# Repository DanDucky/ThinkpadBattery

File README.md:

# ThinkpadBattery
Open source Thinkpad battery design

## Fork scope
- Refactor firmware to make use of some of C++'s templating features to make it more readable and better documented.
- Redesign board to use a thermistor and connect directly to the 7 pin connector. Possibly use a battery gas gauge.
- Redesign case to more cleanly incorporate the board and a recommended BMS.
- Provide better documentation on the Thinkpad's specific smart battery protocol instructions.

## What is this?

This is a fully open source laptop battery design. The design uses an attiny85, which can reply to the T420 motherboard's SMBUS requests.

## Setup

### Configurable Constants

- BATTERY_CAPACITY | Your battery capacity in mAH
- V_HIGH | The highest output voltage of your battery, normally 12.6v
- V_LOW | The cutoff for when the battery will stop working, normally around 10.8v

### Creating your own

Parts Needed
- Arduino Uno/Mega  (for programming the attiny85, Mega needs different pin assignment)
- 12v Lithium-Ion battery pack
- 3S Lithium-Ion BMS (it might be possible to use the existing bms if specification is available but communication needs to be implemented)
- Components from schematic
- PCB from schematic

Once you have all these parts, assemble the pcb and attach a BMS to your battery pack. Solder the 12v battery output/input to the large pads on the pcb, then program the attiny85 with the included ino file. The output pins at the bottom of the PCB are a 1-1 mapping of the motherboard pin input.

### Debugging

- The laptop won't supply power to the board unless it detects there's a battery attached, meaning if you plug the board in to the battery without having an external battery to power it, it won't work.

### Libraries

Use the ATTinyCore for compiling. Without it, Wire.h won't work.

## Limitations

### Voltage Reading / Remaining battery

Currently remaining battery %'s aren't exact because I'm assuming there is a linear coorelation between voltage and capacity (Which is wrong). This is probably fixable using a battery gas gauge, I'll have to investiage more.

### MCU Power Consumption

By design, the MCU will always be on as long as a battery is connected to it. This can cause the battery to slowly run out of power if it isn't connected to a laptop. A potential fix could be to implement a low power mode for the attiny, or have a seperate disconnect switch for the battery power on the battery pack itself.

### 3D Printable Case for T420 only

The case for the cells has been completed. The case model and stl files are included in /model

## Future Plans

iam4722202468 - Design and manufacture a PCB with current,voltage and battery capacity measuring capabilities, an easily programmable microcontroller, and a 3s balanced charger

pj1976 - Find a bms that would fit, or try to talk with bq29312pw that was in the original pack

## Credits

iam4722202468 - Initial work, T420 9 cell model

pj1976 - Added support for R50

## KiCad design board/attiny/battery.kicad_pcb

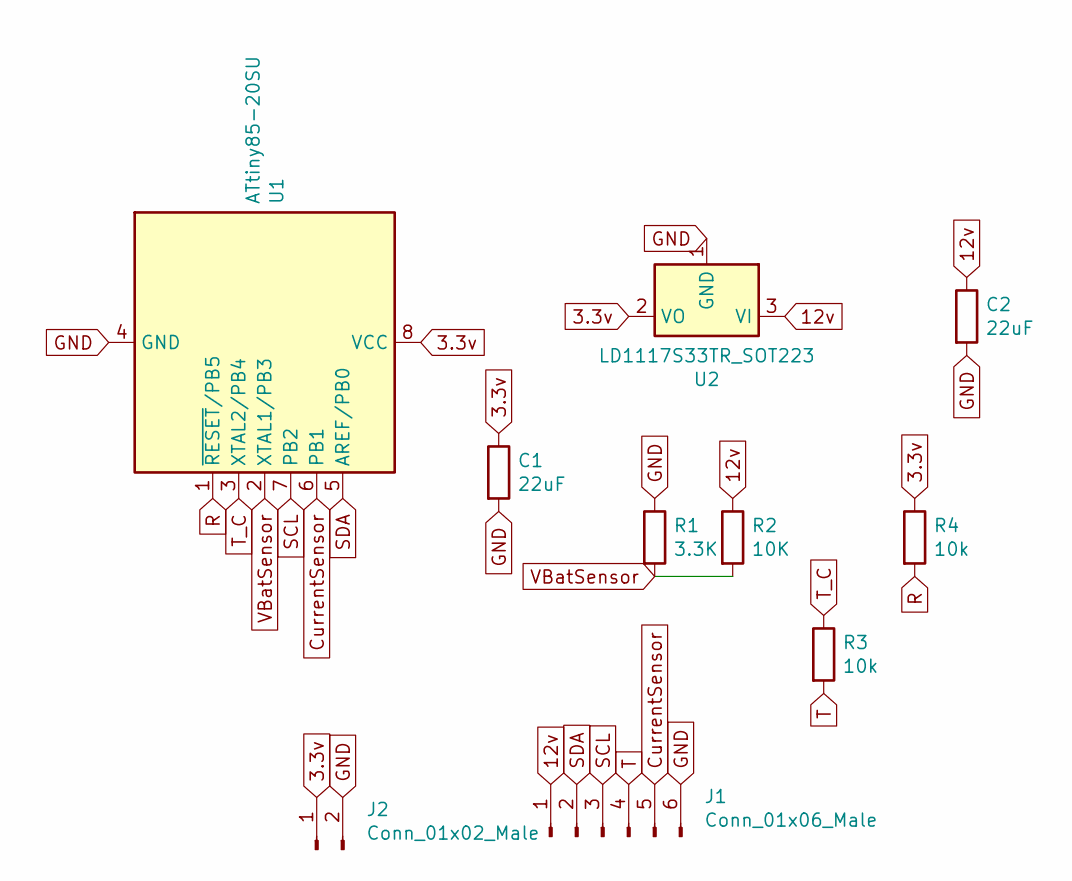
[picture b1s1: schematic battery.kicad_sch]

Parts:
C1, C2: 22uF; C_0805_2012Metric
J1: Conn_01x06_Male; PinHeader_1x06_P2.54mm_Horizontal
J2: Conn_01x02_Male; PinHeader_1x02_P2.54mm_Vertical
R1: 3.3K; R_0402_1005Metric
R2: 10K; R_0402_1005Metric
R3, R4: 10k; R_0402_1005Metric
U1: ATtiny85-20SU; SOIJ-8_5.3x5.3mm_P1.27mm
U2: LD1117S33TR_SOT223; SOT-223-3_TabPin2

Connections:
3.3v: C1.1, J2.1, R4.1, U1.8 (VCC), U2.2 (VO)
12v: C2.1, J1.1, R2.1, U2.3 (VI)
CurrentSensor: J1.5, U1.6 (PB1)
GND: C1.2, C2.2, J1.6, J2.2, R1.1, U1.4 (GND), U2.1 (GND)
R: R4.2, U1.1 (~RESET/PB5)
SCL: J1.3, U1.7 (PB2)
SDA: J1.2, U1.5 (AREF/PB0)
T: J1.4, R3.2
T_C: R3.1, U1.3 (XTAL2/PB4)
VBatSensor: R1.2, R2.2, U1.2 (XTAL1/PB3)

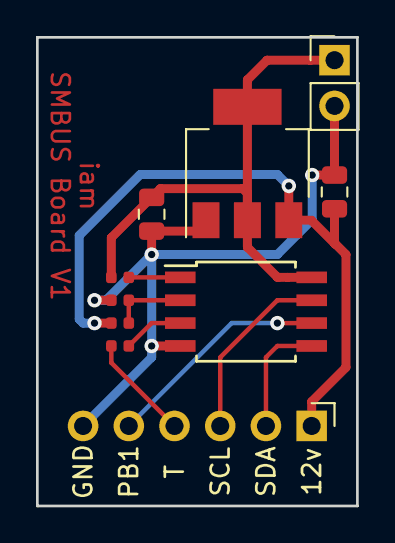
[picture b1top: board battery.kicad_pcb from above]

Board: 2 copper layers, 17.8 x 26.0 mm, 10 parts (0 on the bottom side), 10 nets.

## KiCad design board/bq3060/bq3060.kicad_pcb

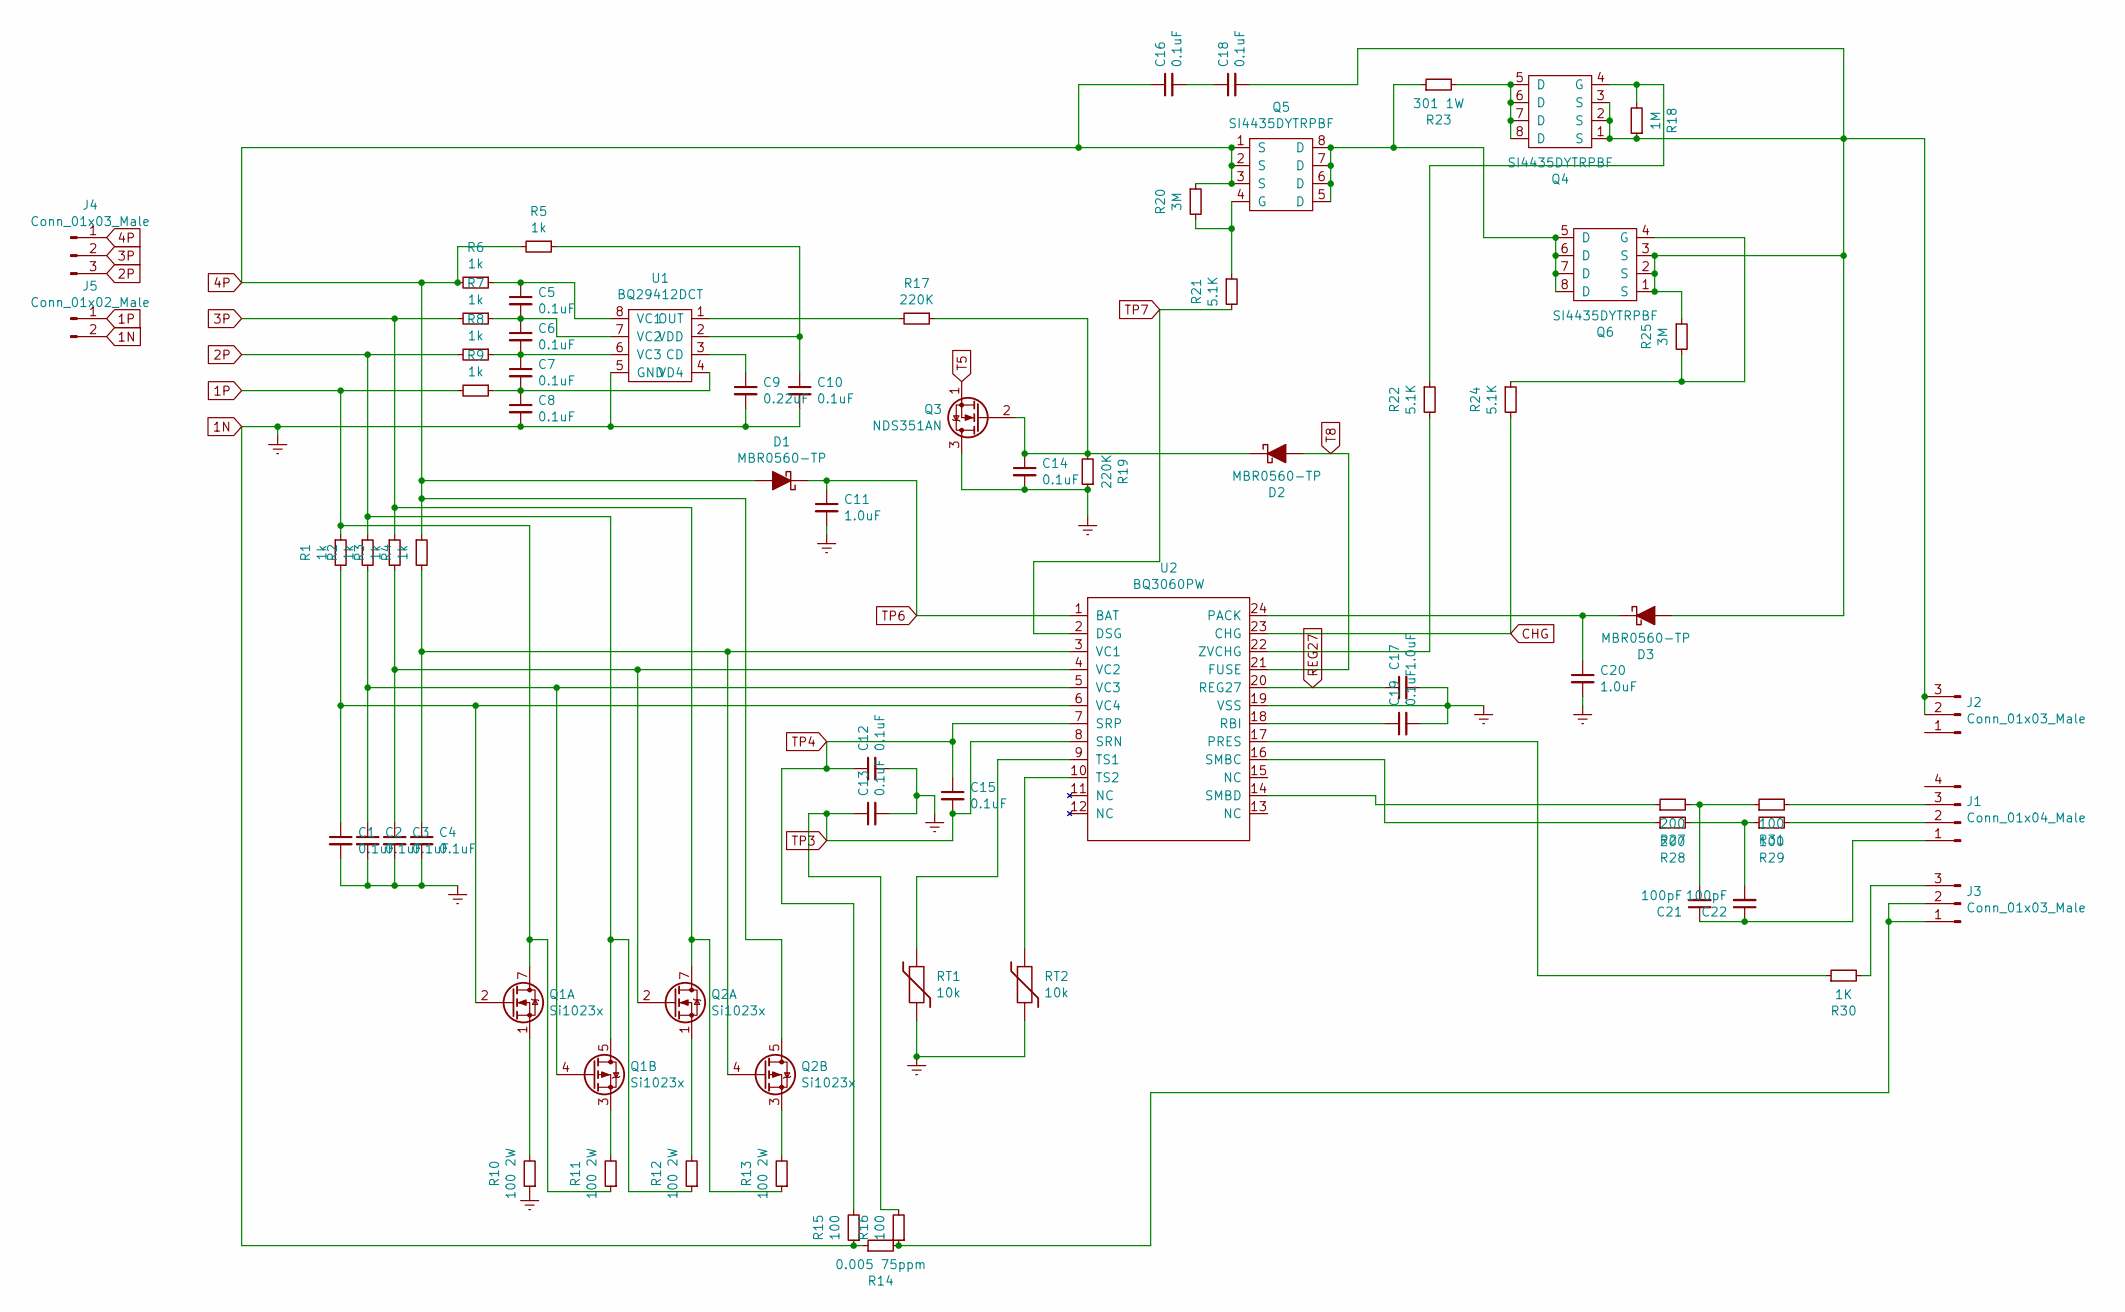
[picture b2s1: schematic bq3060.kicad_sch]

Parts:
C1, C2, C3, C4, C5, C6, C7, C8, C10, C12, C13, C14, C15, C16, C18, C19: 0.1uF; C_0805_2012Metric_Pad1.15x1.40mm_HandSolder
C9: 0.22uF; C_0805_2012Metric_Pad1.15x1.40mm_HandSolder
C11, C17, C20: 1.0uF; C_0805_2012Metric_Pad1.15x1.40mm_HandSolder
C21, C22: 100pF; C_0805_2012Metric_Pad1.15x1.40mm_HandSolder
D1, D2, D3: MBR0560-TP; D_SOD-123
J1: Conn_01x04_Male; PinHeader_1x04_P2.54mm_Horizontal
J2, J3: Conn_01x03_Male; PinHeader_1x03_P2.54mm_Vertical
J4: Conn_01x03_Male; SolderWirePad_1x03_P5.715mm_Drill2mm
J5: Conn_01x02_Male; SolderWirePad_1x02_P7.62mm_Drill2mm
Q1, Q2: Si1023x; SOIC-8_3.9x4.9mm_P1.27mm
Q3: NDS351AN; SOT-23
Q4, Q5, Q6: SI4435DYTRPBF; SOIC-8_3.9x4.9mm_P1.27mm
R1, R2, R3, R4, R5, R6, R7, R8, R9: 1k; R_0805_2012Metric_Pad1.15x1.40mm_HandSolder
R10, R11, R12, R13: 100 2W; R_2512_6332Metric_Pad1.52x3.35mm_HandSolder
R14: 0.005 75ppm; R_2512_6332Metric_Pad1.52x3.35mm_HandSolder
R15, R16, R29, R31: 100; R_0805_2012Metric_Pad1.15x1.40mm_HandSolder
R17, R19: 220K; R_0805_2012Metric_Pad1.15x1.40mm_HandSolder
R18: 1M; R_0805_2012Metric_Pad1.15x1.40mm_HandSolder
R20, R25: 3M; R_0805_2012Metric_Pad1.15x1.40mm_HandSolder
R21, R22, R24: 5.1K; R_0805_2012Metric_Pad1.15x1.40mm_HandSolder
R23: 301 1W; R_2512_6332Metric_Pad1.52x3.35mm_HandSolder
R27, R28: 200; R_0805_2012Metric_Pad1.15x1.40mm_HandSolder
R30: 1K; R_0805_2012Metric_Pad1.15x1.40mm_HandSolder
RT1, RT2: 10k; R_0805_2012Metric_Pad1.15x1.40mm_HandSolder
U1: BQ29412DCT; SN74LVC2G241_DCT_8
U2: BQ3060PW; TSSOP-24_4.4x7.8mm_P0.65mm

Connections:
1N: C1.2, C2.2, C3.2, C4.2, C8.2, C9.2, C10.2, C11.2, C12.2, C13.2, C14.2, C17.2, C19.2, C20.2, J5.2, Q3.3 (D), R10.1, R14.1, R15.1, R19.1, RT1.2, RT2.2, U1.5 (GND), U2.19 (VSS)
1P: J5.1, Q1.7 (D1), Q1.8 (D1), R1.1, R9.2, R11.1
2P: J4.3, Q1.5 (D2), Q1.6 (D2), R2.1, R8.2, R12.1
3P: J4.2, Q2.7 (D1), Q2.8 (D1), R3.1, R7.2, R13.1
4P: C16.1, D1.2 (A), J4.1, Q2.5 (D2), Q2.6 (D2), Q5.1 (S), Q5.2 (S), Q5.3 (S), R4.1, R5.2, R6.2, R20.1
CHG: R24.2, U2.23 (CHG)
unnamed: C1.1, Q1.2 (G1), R1.2, U2.6 (VC4)
unnamed: C2.1, Q1.4 (G2), R2.2, U2.5 (VC3)
unnamed: C3.1, Q2.2 (G1), R3.2, U2.4 (VC2)
unnamed: C4.1, Q2.4 (G2), R4.2, U2.3 (VC1)
unnamed: C5.1, R6.1, U1.8 (VC1)
unnamed: C5.2, C6.1, R7.1, U1.7 (VC2)
unnamed: C6.2, C7.1, R8.1, U1.6 (VC3)
unnamed: C7.2, C8.1, R9.1, U1.4 (VD4)
unnamed: C9.1, U1.3 (CD)
unnamed: C10.1, R5.1, U1.2 (VDD)
unnamed: C14.1, D2.1 (K), Q3.2 (G), R17.1, R19.2
unnamed: C16.2, C18.1
unnamed: C18.2, D3.2 (A), J2.2, J2.3, Q4.1 (S), Q4.2 (S), Q4.3 (S), Q6.1 (S), Q6.2 (S), Q6.3 (S), R18.1, R25.1
unnamed: C19.1, U2.18 (RBI)
unnamed: C20.1, D3.1 (K), U2.24 (PACK)
unnamed: C21.1, C22.1, J1.1
unnamed: C21.2, R27.2, R31.1
unnamed: C22.2, R28.2, R29.1
unnamed: J1.2, R29.2
unnamed: J1.3, R31.2
unnamed: J3.1, J3.2, R14.2, R16.1
unnamed: J3.3, R30.2
unnamed: Q1.1 (S1), R10.2
unnamed: Q1.3 (S2), R11.2
unnamed: Q2.1 (S1), R12.2
unnamed: Q2.3 (S2), R13.2
unnamed: Q4.4 (G), R18.2, R22.1
unnamed: Q4.5 (D), Q4.6 (D), Q4.7 (D), Q4.8 (D), R23.2
unnamed: Q5.4 (G), R20.2, R21.1
unnamed: Q5.5 (D), Q5.6 (D), Q5.7 (D), Q5.8 (D), Q6.5 (D), Q6.6 (D), Q6.7 (D), Q6.8 (D), R23.1
unnamed: Q6.4 (G), R24.1, R25.2
unnamed: R17.2, U1.1 (OUT)
unnamed: R22.2, U2.22 (ZVCHG)
unnamed: R27.1, U2.14 (SMBD)
unnamed: R28.1, U2.16 (SMBC)
unnamed: R30.1, U2.17 (PRES)
unnamed: RT1.1, U2.9 (TS1)
unnamed: RT2.1, U2.10 (TS2)
REG27: C17.1, U2.20 (REG27)
T5: Q3.1 (S)
T8: D2.2 (A), U2.21 (FUSE)
TP3: C13.1, C15.2, R16.2, U2.8 (SRN)
TP4: C12.1, C15.1, R15.2, U2.7 (SRP)
TP6: C11.1, D1.1 (K), U2.1 (BAT)
TP7: R21.2, U2.2 (DSG)

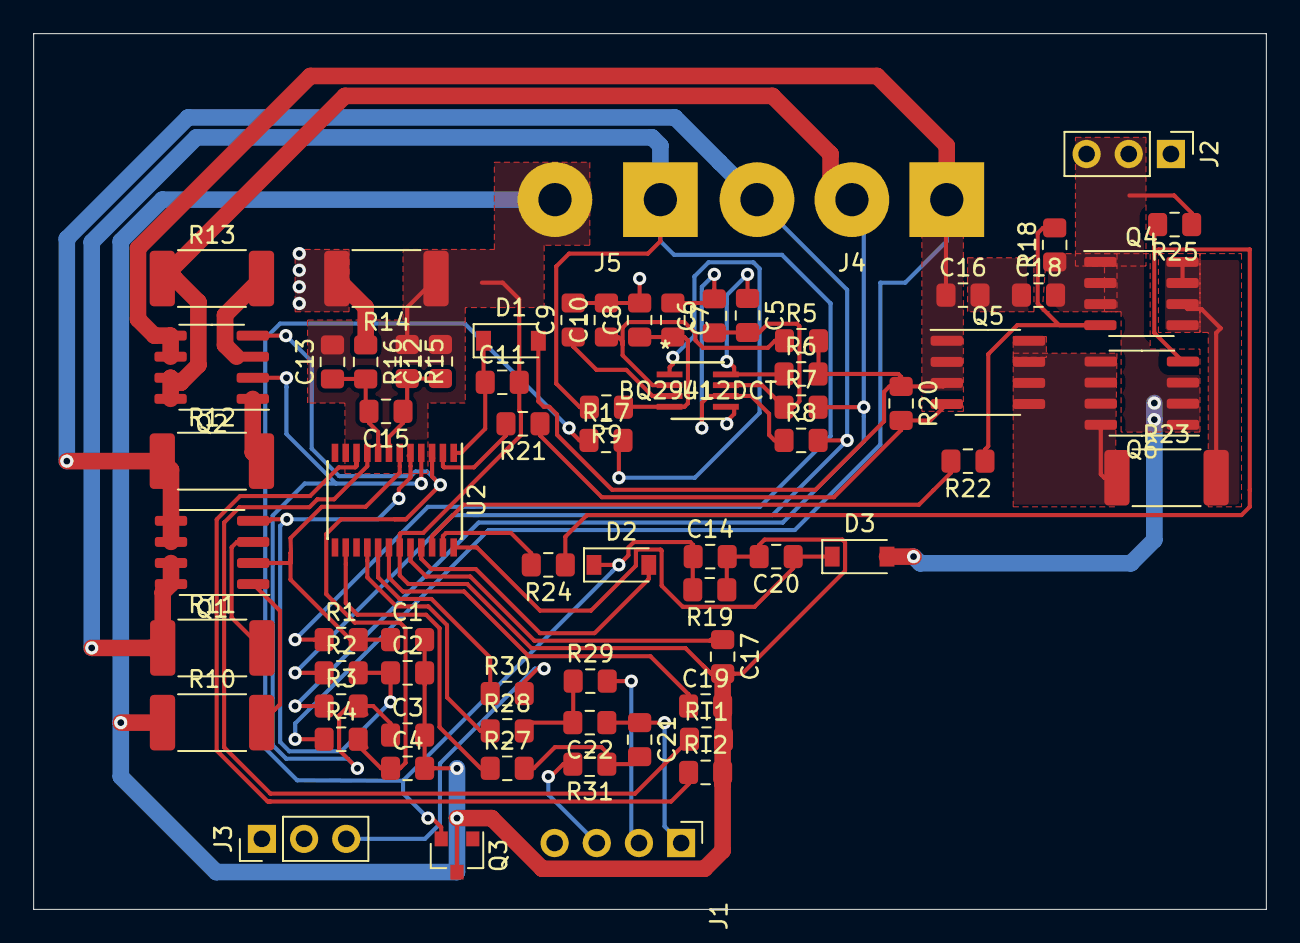
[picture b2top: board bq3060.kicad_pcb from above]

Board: 2 copper layers, 74.2 x 52.8 mm, 70 parts (0 on the bottom side), 50 nets.

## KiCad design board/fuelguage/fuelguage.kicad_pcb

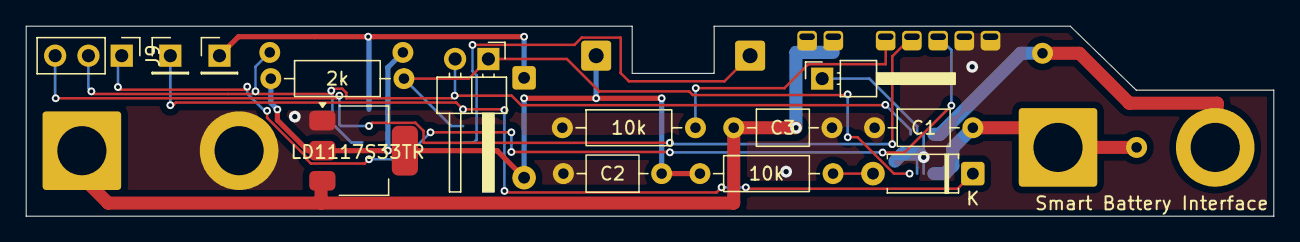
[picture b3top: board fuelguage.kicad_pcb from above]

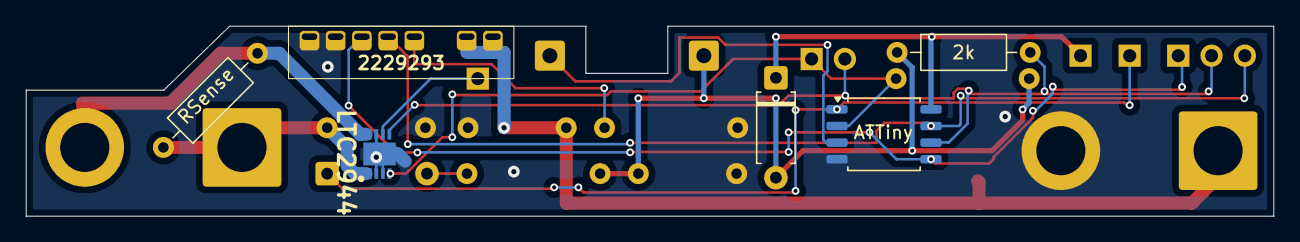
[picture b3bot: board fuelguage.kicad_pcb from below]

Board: 2 copper layers, 95.2 x 14.5 mm, 23 parts (6 on the bottom side), 15 nets.

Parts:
2k, 2k#2: 2k; R_Axial_DIN0207_L6.3mm_D2.5mm_P10.16mm_Horizontal
10k, 10k#2: 10k; R_Axial_DIN0207_L6.3mm_D2.5mm_P10.16mm_Horizontal
2229293: 2229293-1_vertical
ATTiny: ATtiny85-20SU; SOIC-8_5.3x5.3mm_P1.27mm
C1: 0.001; C_Axial_L3.8mm_D2.6mm_P7.50mm_Horizontal
C2, C3: 0.022; C_Axial_L3.8mm_D2.6mm_P7.50mm_Horizontal
D1, D2: 1N4007; D_A-405_P7.62mm_Horizontal
J1, J12: Conn_01x02_Socket; SolderWire-4sqmm_1x02_P12mm_D3mm_OD6mm
J4: Conn_01x02_Pin; PinHeader_1x02_P2.54mm_Horizontal
J6: Conn_01x01_Pin; PinHeader_1x01_P2.54mm_Horizontal
J7, J11: Conn_01x01_Pin; PinHeader_1x01_P2.54mm_Vertical
J8, J10: Conn_01x01_Socket; SolderWire-0.5sqmm_1x01_D0.9mm_OD2.3mm
J9: Conn_01x03_Pin; PinHeader_1x03_P2.54mm_Vertical
LD1117S33TR: LD1117S33TR_SOT223; SOT-223-3_TabPin2
LTC2944: LTC2944IDD#PBF; LTC2944
RSense: 50m; R_Axial_DIN0207_L6.3mm_D2.5mm_P10.16mm_Horizontal

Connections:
3.3v: 2k.1, 2k#2.1, 10k#2.1, C2.1, D2.2 (A), J10.1, LD1117S33TR.2 (VO)
12v: 2229293.0 (+), C3.1, J1.1, LD1117S33TR.3 (VI)
GND: 10k.1, 2229293.6 (-), ATTiny.4 (GND), C1.1, C2.2, C3.2, J1.2, LD1117S33TR.1 (GND), LTC2944.2 (GND_1), LTC2944.3 (GND_2), LTC2944.7 (GND_3), LTC2944.9 (EP)
unnamed: 10k#2.2, D1.2 (A)
unnamed: ATTiny.1 (~RESET/PB5), D1.1 (K), J7.1
unnamed: ATTiny.8 (VCC), D2.1 (K), J11.1
unnamed: 2k.2, ATTiny.2 (XTAL1/PB3), J4.1, LTC2944.4 (SCL)
unnamed: 2k#2.2, ATTiny.6 (PB1), J4.2, J9.2, LTC2944.5 (SDA)
unnamed: C1.2, J12.1, LTC2944.1 (SENSE+), RSense.1
unnamed: J12.2, LTC2944.8 (SENSE-), RSense.2
unnamed: J6.1, LTC2944.6 (~ALCC)
unnamed: ATTiny.3 (XTAL2/PB4), J8.1
unnamed: 2229293.3 (SDA), ATTiny.5 (AREF/PB0), J9.1
unnamed: 2229293.2 (SCL), ATTiny.7 (PB2), J9.3
unnamed: 10k.2, 2229293.1 (thermistor)

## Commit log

2025-05-24 quick reformat
2025-05-27 dev board

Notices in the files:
parts and their libraries:
Copyright 2016 Accelerated Designs. All rights reserved.
